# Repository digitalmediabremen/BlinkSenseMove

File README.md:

# Blink Sense Move.

A general purpose PCB/Toolkit for easy usage of sensors and actuators

# Hardware

1. maximum PCB dimensions: 100×100mm ( = 1,76/10pcs @[jlcpcb](http://jlcpcb.com) )
2. uses teensy 3.2 as mcu
3. features
  - 2 mosfets
  - h-bridge
  - amplfiers for external sensors
  - display (only dotmatrix for now, v2 will also offer pins for oled)
  - stepperdriver
  - clean audio output with lpf
  - potentiometers
  - buttons
  - patchable io
  
4. version 2 will feature
  - midi
  - choice of display
  - possibly cleaner powersolution

-----
## Pre v01

## MCU-Ideas

( supported by Arduino IDE )

1. ATmega328p (AVR, 20 MHz, 8-bit, @as_used_in(Arduino UNO)), pP 1.60€, [Datasheet](http://www.microchip.com/mymicrochip/filehandler.aspx?ddocname=en589666)
2. NXP MK20DX256 (ARM Cortex-M4, 96 MHz, 32-bit, @as_used_in(Teensy 3.2) ), pP 9.00€, [Datasheet](https://www.pjrc.com/teensy/K20P64M72SF1.pdf)
3. STM32F446RE (ARM Cortex-M4, 180 MHz, 32-bit, @as_used_in(Nucleo F446RE + Arduino for STM32)), pP 9.00€, [Datasheet](http://www.st.com/content/ccc/resource/technical/document/datasheet/65/cb/75/50/53/d6/48/24/DM00141306.pdf/files/DM00141306.pdf/jcr:content/translations/en.DM00141306.pdf)

### Boards

1) Teensy LC (approx 13 Euro) | Teensy 3.2 (Pro: Fast, Audiocapabilitys. Contra: Not super cheap)
2) Arduino Nano (Pro: Compatibilty, cheap. Contra: CH340-Driver issue with cheap Variations)

## Ideas for Features

1) Felix´ Audio Output board
2) 1 or 2 Mosfets with Diodes
3) 12v Input with good Quality Voltage converter
4) Stepper Motor Driver
5) H-Bridge
6) 7-Segment-Display
7) Add-On-Interface for stuff like Encoders or Analogsticks and similiar stuff.
8) motor board *only* ( H-bridge+mosfet, stepper-driver, PWM for high-current/loads )
9) Making the wiring Modular
10) Mic- and Piezoamp, maybe also a switchable direct out to Felix Audio out.
11) frequency devider / counter ic
12) Making it modular (plugging and using boards together, with one microcontroller)
13) encoder
14) 2 potis

## Bill of materials
- 3.5 mm jack
- AKL
- 595 (SMD?)
- IRF530 (SMD)
- 7seg/4Digit
- spannungsregler MC7805CD2TG (SMD) (1A 5V für teensy und externe komponenten)

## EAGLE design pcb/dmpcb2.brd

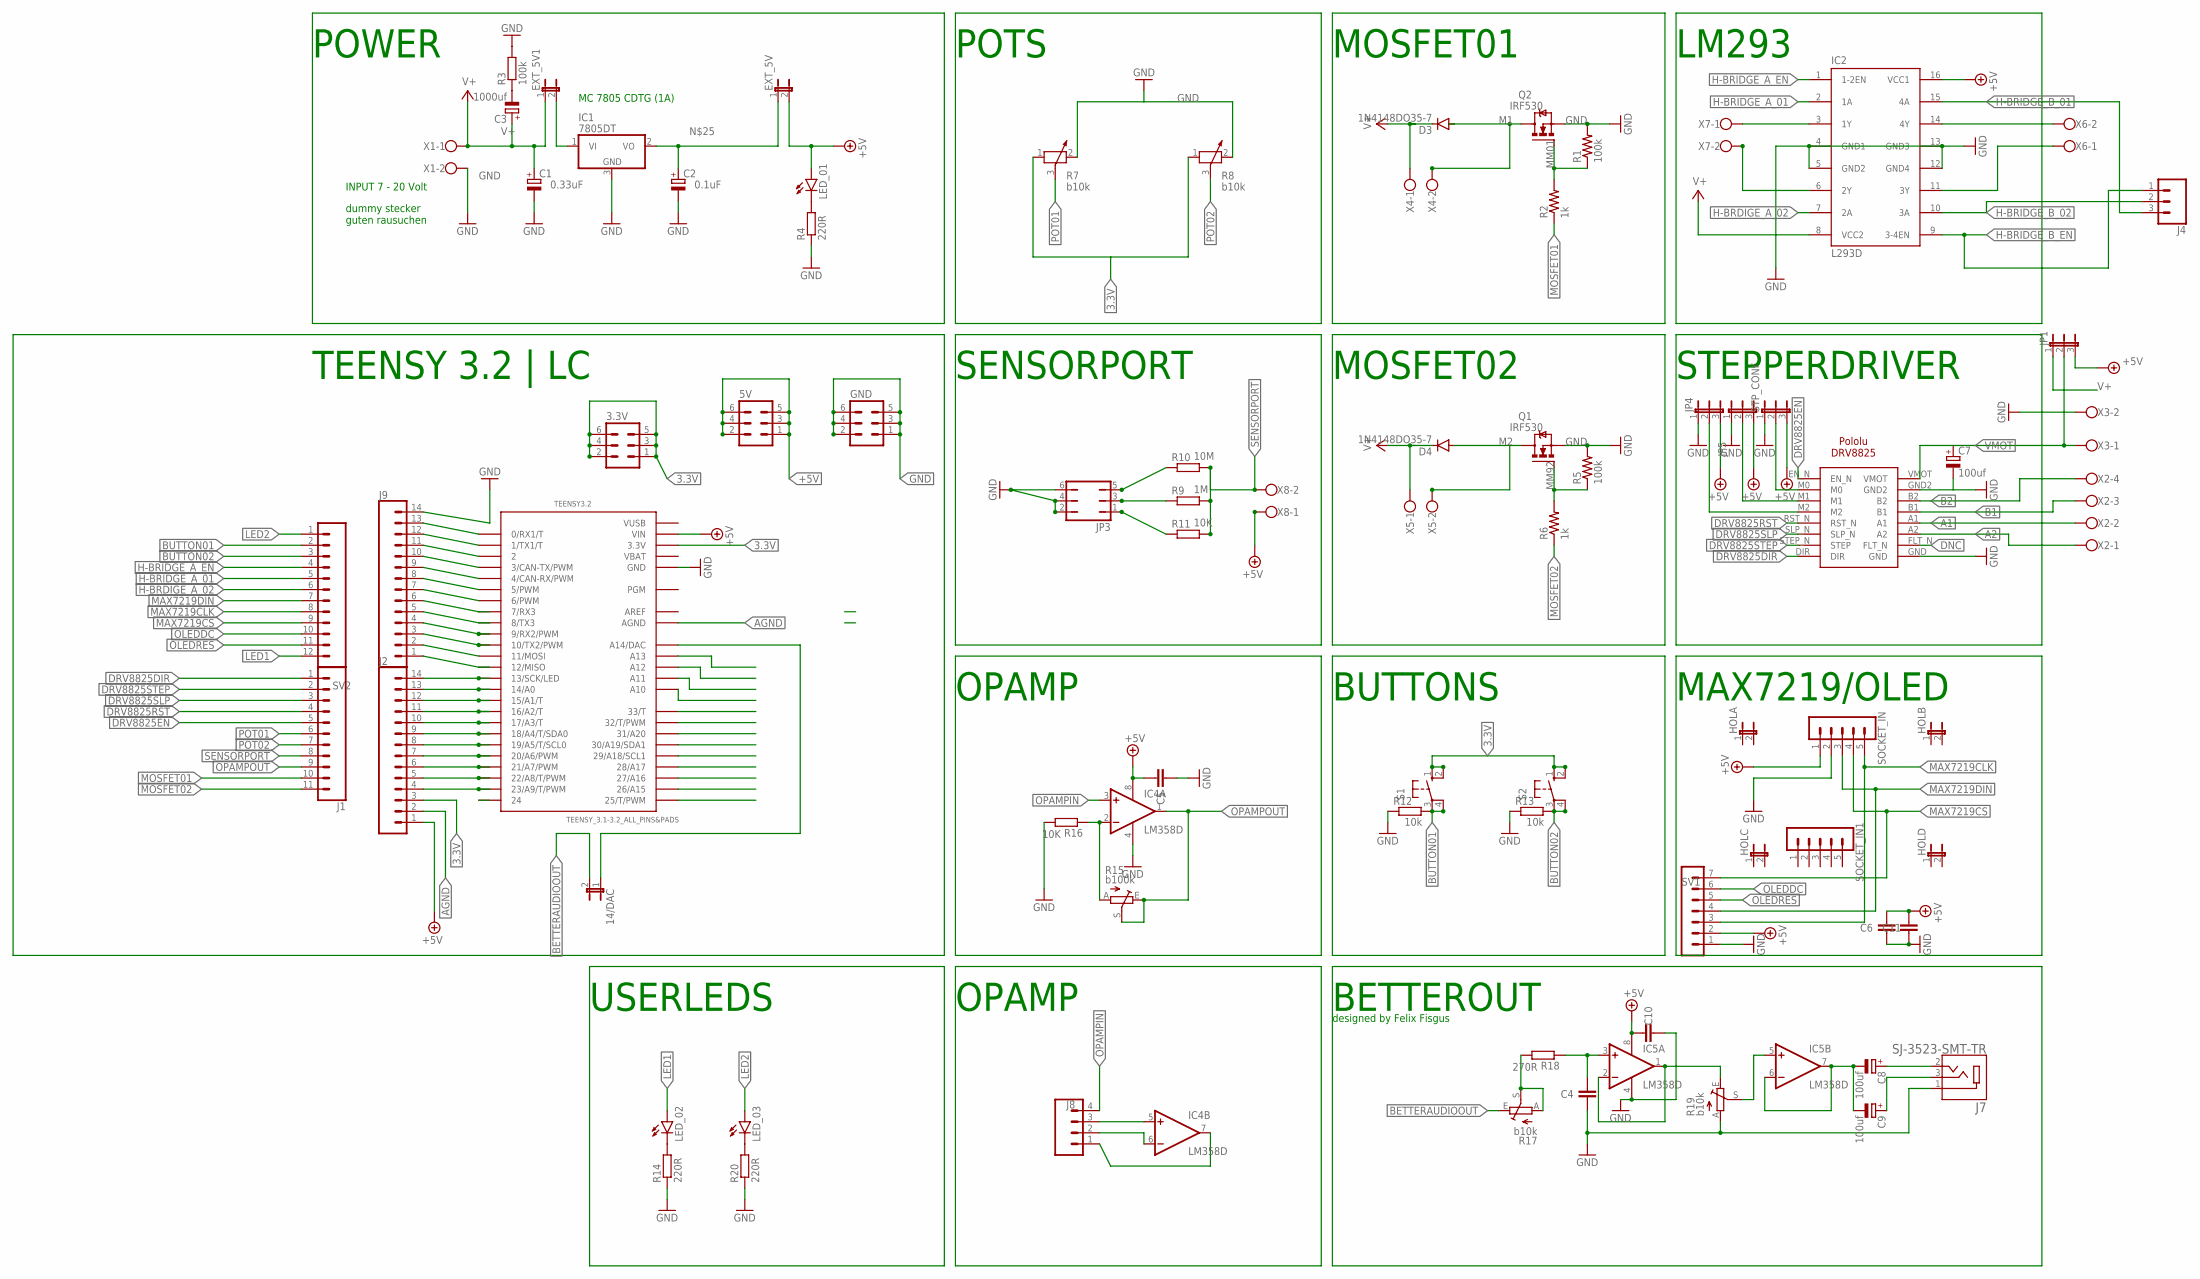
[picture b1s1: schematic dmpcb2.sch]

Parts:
3.3V, 5V: MA03-2
14/DAC: JP1E; JP1
C1: 0.33uF; SANYO-OSCON_A'
C2: 0.1uF; SANYO-OSCON_A'
C3: 1000uf; E3,5-8
C4, C5, C6, C10: 100nf; C0805
C7, C8, C9: 100uf; E5-5
C11: 10uf; C0805
D3, D4: 1N4148DO35-7; DO35-7
DRV8825: POLOLU-DRV8825
EXT_5V, EXT_5V1: JP1E; JP1
GND: MA03-2
HOLA: JP1E; JP1
HOLB: JP1E; JP1
HOLC: JP1E; JP1
HOLD: JP1E; JP1
IC1: 7805DT; TO252
IC2: L293D; DIL16
IC4, IC5: LM358D; SO08
J1: CONN_11; 1X11
J2, J9: CONN_14; 1X14
J4: CONN_03LOCK_LONGPADS; 1X03_LOCK_LONGPADS
J7: SJ-3523-SMT-TR; CUI_SJ-3523-SMT-TR
J8: CONN_04; 1X04
JP1, JP4, JP5: JP2E; JP2
JP3: JP3Q
LED_01, LED_02, LED_03: LEDSML0805; SML0805
Q1, Q2: IRF530; TO220BV
R1, R3, R5: 100k; R0805
R2, R6: 1k; R0805
R4, R14, R20: 220R; R0805
R7, R8: b10k; PT-10
R9: 1M; M0805
R10: 10M; M0805
R11, R16: 10K; M0805
R12, R13: 10k; M0805
R15: b100k; RJ9W
R17, R19: b10k; RJ9W
R18: 270R; M0805
S1, S2: 10-XX; B3F-10XX
SOCKET_IN, SOCKET_IN1: MA05-1
STP_CONF: JP2E; JP2
SV1: MA07-1
SV2: CONN_12; 1X12
TEENSY3.2: TEENSY_3.1-3.2_ALL_PINS&PADS; TEENSY_3.0-3.2_ALL_PINS_&_PADS
X1, X3, X4, X5, X6, X7, X8: W237-102
X2: W237-4

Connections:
3.3V: 3.3V.1, 3.3V.2, 3.3V.3, 3.3V.4, 3.3V.5, 3.3V.6, J2.3, R7.1, R8.1, S1.1 (S), S1.2 (S1), S2.1 (S), S2.2 (S1), TEENSY3.2.3.3V, TEENSY3.2.3.3V1 (3.3V), TEENSY3.2.3.3V2 (3.3V)
+5V: 5V.1, 5V.2, 5V.3, 5V.4, 5V.5, 5V.6, C5.1, C6.1, C10.2, C11.1, EXT_5V.2, IC2.16 (VCC1), IC4.8 (V+), IC5.8 (V+), J2.1, JP1.3, JP4.3, JP5.3, LED_01.A, SOCKET_IN.1, STP_CONF.3, SV1.2, TEENSY3.2.VIN, X8.1
A1: DRV8825.A1, X2.2
A2: DRV8825.A2, X2.1
AGND: J2.2, TEENSY3.2.AGND
AREF: TEENSY3.2.AREF
B1: DRV8825.B1, X2.3
B2: DRV8825.B2, X2.4
BETTERAUDIOOUT: 14/DAC.2, R17.E
BUTTON01: R12.2, S1.3, S1.4 (P1), SV2.2
BUTTON02: R13.2, S2.3, S2.4 (P1), SV2.3
DNC: DRV8825.FLT_N
DRV8825DIR: DRV8825.DIR, J1.1
DRV8825EN: DRV8825.EN_N, J1.5
DRV8825RST: DRV8825.RST_N, J1.4
DRV8825SLP: DRV8825.SLP_N, J1.3
DRV8825STEP: DRV8825.STEP_N (STEP), J1.2
GND: C1.-, C2.-, C4.2, C5.2, C6.2, C7.-, C10.1, C11.2, DRV8825.GND, DRV8825.GND2, GND.1, GND.2, GND.3, GND.4, GND.5, GND.6, IC1.3 (GND), IC2.4 (GND1), IC2.5 (GND2), IC2.12 (GND4), IC2.13 (GND3), IC4.4 (V-), IC5.4 (V-), J7.1, J9.14, JP3.2, JP3.4, JP3.6, JP4.1, JP5.1, Q1.S, Q2.S, R1.2, R3.2, R4.1, R5.2, R7.2, R8.2, R12.1, R13.1, R14.1, R16.2, R19.A, R20.1, SOCKET_IN.2, STP_CONF.1, SV1.1, TEENSY3.2.GND, TEENSY3.2.GND1 (GND), TEENSY3.2.GND2 (GND), X1.2, X3.2
H-BRDIGE_A_02: IC2.7 (2A), SV2.6
H-BRIDGE_A_01: IC2.2 (1A), SV2.5
H-BRIDGE_A_EN: IC2.1 (1-2EN), SV2.4
H-BRIDGE_B_01: IC2.15 (4A), J4.3
H-BRIDGE_B_02: IC2.10 (3A), J4.2
H-BRIDGE_B_EN: IC2.9 (3-4EN), J4.1
LED1: LED_02.A, SV2.12
LED2: LED_03.A, SV2.1
M1: D3.A, Q2.D, X4.2
M2: D4.A, Q1.D, X5.2
MAX7219CLK: SOCKET_IN.5, SV1.3, SV2.8
MAX7219CS: SOCKET_IN.4, SV1.7, SV2.9
MAX7219DIN: SOCKET_IN.3, SV1.4, SV2.7
MM01: Q2.G, R1.1, R2.2
MM92: Q1.G, R5.1, R6.2
MOSFET01: J1.10, R2.1
MOSFET02: J1.11, R6.1
unnamed: IC2.3 (1Y), X7.1
unnamed: IC2.6 (2Y), X7.2
unnamed: C3.-, R3.1
unnamed: LED_01.C, R4.2
unnamed: IC2.14 (4Y), X6.2
unnamed: IC2.11 (3Y), X6.1
unnamed: JP3.5, R10.1
unnamed: JP3.3, R9.1
unnamed: JP3.1, R11.1
unnamed: EXT_5V1.2, IC1.1 (VI)
unnamed: IC4.5 (+IN), J8.3
unnamed: J2.4, TEENSY3.2.23/A9 (23/A9/T/PWM)
unnamed: C2.+, EXT_5V.1, IC1.2 (VO)
unnamed: J2.5, TEENSY3.2.22/A8 (22/A8/T/PWM)
unnamed: J2.6, TEENSY3.2.21/A7 (21/A7/PWM)
unnamed: J2.7, TEENSY3.2.20/A6 (20/A6/PWM)
unnamed: J2.8, TEENSY3.2.19/A5 (19/A5/T/SCL0)
unnamed: J2.9, TEENSY3.2.18/A4 (18/A4/T/SDA0)
unnamed: J2.10, TEENSY3.2.17/A3 (17/A3/T)
unnamed: J2.11, TEENSY3.2.16/A2 (16/A2/T)
unnamed: J2.12, TEENSY3.2.15/A1 (15/A1/T)
unnamed: J2.13, TEENSY3.2.14/A0
unnamed: J2.14, TEENSY3.2.13 (13/SCK/LED)
unnamed: J9.1, TEENSY3.2.12 (12/MISO)
unnamed: J9.2, TEENSY3.2.11 (11/MOSI)
unnamed: J9.3, TEENSY3.2.10 (10/TX2/PWM)
unnamed: J9.4, TEENSY3.2.9 (9/RX2/PWM)
unnamed: J9.5, TEENSY3.2.8 (8/TX3)
unnamed: J9.6, TEENSY3.2.7 (7/RX3)
unnamed: 14/DAC.1, TEENSY3.2.RESET/DAC (A14/DAC)
unnamed: DRV8825.M2, JP4.2
unnamed: DRV8825.M1, JP5.2
unnamed: DRV8825.M0, STP_CONF.2
unnamed: J9.12, TEENSY3.2.1 (1/TX1/T)
unnamed: J9.13, TEENSY3.2.0 (0/RX1/T)
unnamed: IC4.2 (-IN), R15.A, R16.1
unnamed: LED_02.C, R14.2
unnamed: C8.+, J7.2
unnamed: R17.A, R17.S, R18.2
unnamed: C4.1, IC5.3 (+IN), R18.1
unnamed: IC5.1 (OUT), IC5.2 (-IN), R19.E
unnamed: IC4.6 (-IN), J8.2
unnamed: IC5.5 (+IN), R19.S
unnamed: C8.-, C9.-, IC5.6 (-IN), IC5.7 (OUT)
unnamed: C9.+, J7.3
unnamed: IC4.7 (OUT), J8.1
unnamed: LED_03.C, R20.2
OLEDDC: SV1.6, SV2.10
OLEDRES: SV1.5, SV2.11
OPAMPIN: IC4.3 (+IN), J8.4
OPAMPOUT: IC4.1 (OUT), J1.9, R15.E, R15.S
PIN2: J9.11, TEENSY3.2.2
PIN3: J9.10, TEENSY3.2.3 (3/CAN-TX/PWM)
PIN4: J9.9, TEENSY3.2.4 (4/CAN-RX/PWM)
PIN5: J9.8, TEENSY3.2.5 (5/PWM)
PIN6: J9.7, TEENSY3.2.6 (6/PWM)
POT01: J1.6, R7.3
POT02: J1.7, R8.3
SENSORPORT: J1.8, R9.2, R10.2, R11.2, X8.2
V+: C1.+, C3.+, D3.C, D4.C, EXT_5V1.1, IC2.8 (VCC2), JP1.1, X1.1, X4.1, X5.1
VBAT: TEENSY3.2.VBAT
VMOT: C7.+, DRV8825.VMOT, JP1.2, X3.1
VUSB: TEENSY3.2.VUSB

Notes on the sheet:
POWER
INPUT 7 - 20 Volt
MC 7805 CDTG (1A)
TEENSY 3.2 | LC
dummy stecker guten rausuchen
MOSFET01
LM293
MOSFET02
POTS
STEPPERDRIVER
SENSORPORT
BUTTONS
MAX7219/OLED
OPAMP
BETTEROUT
designed by Felix Fisgus
USERLEDS

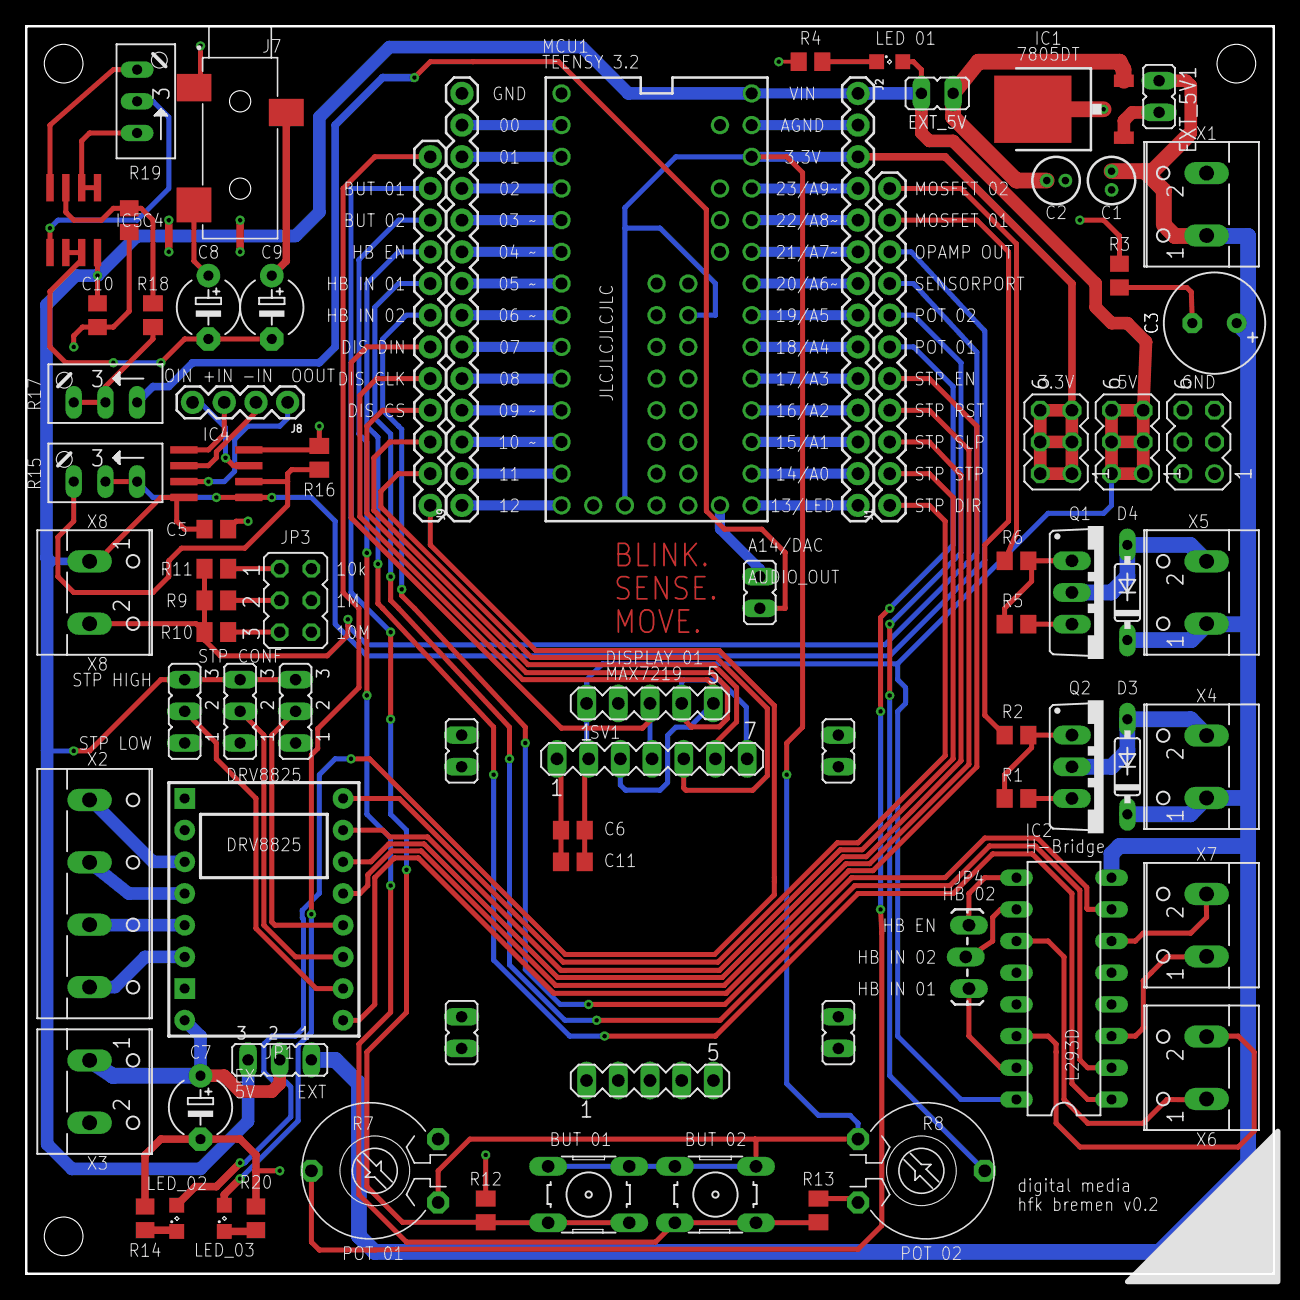
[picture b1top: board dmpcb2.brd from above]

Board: 2 copper layers, 100.0 x 100.0 mm, 79 parts (0 on the bottom side), 94 nets.

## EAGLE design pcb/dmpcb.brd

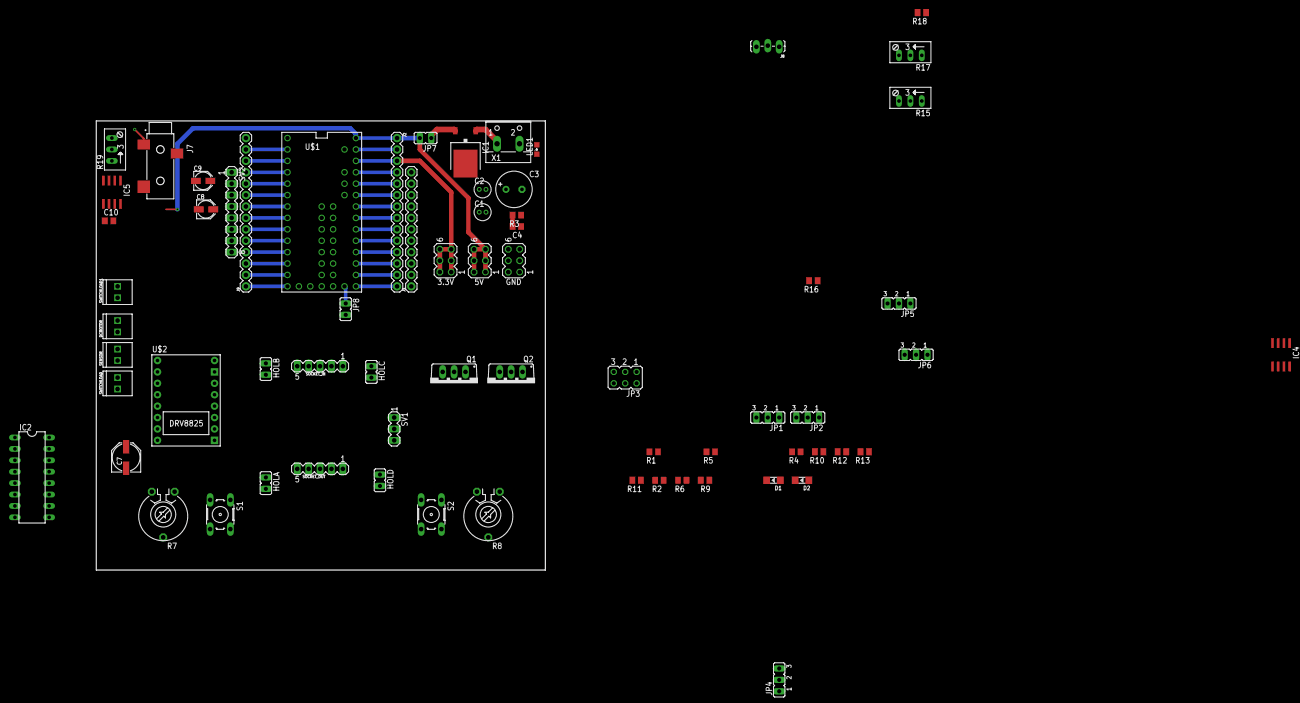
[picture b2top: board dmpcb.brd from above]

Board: 2 copper layers, 100.0 x 100.0 mm, 68 parts (0 on the bottom side), 80 nets.

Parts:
3.3V, 5V: MA03-2
C1: 0.33uF; SANYO-OSCON_A'
C2: 0.1uF; SANYO-OSCON_A'
C3: 1000uf; E3,5-8
C4, C10: 100nf; C0805
C7: 100uf; PANASONIC_D
C8, C9: 100uf; PANASONIC_B
D1, D2: 1N4148; LL-34
DCMOTOR: 1X02_2.54_SCREWTERM
GND: MA03-2
HOLA: JP1
HOLB: JP1
HOLC: JP1
HOLD: JP1
IC1: 7805DT; TO252
IC2: L293D; DIL16
IC4, IC5: LM358D; SO08
J1: 1X11
J2, J9: 1X14
J7: SJ-3523-SMT-TR; CUI_SJ-3523-SMT-TR
J8: 1X03_LOCK_LONGPADS
JP1, JP2, JP4, JP5, JP6: JP2
JP3: JP3Q
JP7, JP8: JP1
LED1: SML0805
Q1, Q2: IRF530; TO220BV
R1, R3, R5: 100k; R0805
R2, R6: 1k; R0805
R4: 220; R0805
R7, R8: b10k; PT-10
R9: 1M; M0805
R10: 10M; M0805
R11, R16: 10K; M0805
R12, R13: 10k; M0805
R15: b100k; RJ9W
R17, R19: b10k; RJ9W
R18: 270R; M0805
S1, S2: B3F-10XX
SENSOR: 1X02_2.54_SCREWTERM
SOCKET_IN: MA05-1
SOCKET_OUT: MA05-1
SV1: MA03-1
SV2: MA08-1
SWITCHLOAD, SWITCHLOAD1: 1X02_2.54_SCREWTERM
U$1: TEENSY_3.1-3.2_ALL_PINS&PADS; TEENSY_3.0-3.2_ALL_PINS_&_PADS
U$2: POLOLU-DRV8825
X1: W237-102

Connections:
3.3V: 3.3V.1, 3.3V.2, 3.3V.3, 3.3V.4, 3.3V.5, 3.3V.6, J2.3, R7.1, R8.1, U$1.3.3V, U$1.3.3V1, U$1.3.3V2
+5V: 5V.1, 5V.2, 5V.3, 5V.4, 5V.5, 5V.6, C10.2, IC2.16, IC4.8, IC5.8, J2.1, JP4.3, JP5.3, JP6.3, JP7.2, SENSOR.P2, SOCKET_IN.1, U$1.VIN
AGND: J2.2, U$1.AGND
BETTERAUDIOOUT: JP8.2, R17.E
BUTTON01: R12.2, S1.3, S1.4, SV2.1
BUTTON02: R13.2, S2.3, S2.4, SV2.2
D: JP1.2, JP2.2, Q1.D, Q2.D, SWITCHLOAD.P1, SWITCHLOAD1.P1
DRV8825DIR: J1.2, U$2.DIR
DRV8825EN: J1.1, U$2.EN_N
DRV8825RST: J1.4, U$2.RST_N
DRV8825SLP: J1.5, U$2.SLP_N
DRV8825STEP: J1.3, U$2.STEP_N
G: Q1.G, Q2.G, R1.1, R2.2, R5.1, R6.2
GND: C1.-, C2.-, C4.2, C7.-, C10.1, GND.1, GND.2, GND.3, GND.4, GND.5, GND.6, IC1.3, IC2.4, IC2.5, IC2.12, IC2.13, IC4.4, IC5.4, J7.1, J9.14, JP3.2, JP3.4, JP3.6, JP4.1, JP5.1, JP6.1, R3.2, R4.1, R7.2, R8.2, R12.1, R13.1, R16.2, R19.A, SOCKET_IN.2, U$1.GND, U$1.GND1, U$1.GND2, U$2.GND, U$2.GND2, X1.2
LM293EN: IC2.1, SV2.3
LM293IN01: IC2.2, SV2.4
LM293IN02: IC2.7, SV2.5
MAX7219CLK: SOCKET_IN.5, SV1.1, SV2.7
MAX7219CS: SOCKET_IN.4, SV1.2, SV2.8
MAX7219DIN: SOCKET_IN.3, SV1.3, SV2.6
MOSFET01: J1.10, R2.1
MOSFET02: J1.11, R6.1
unnamed: DCMOTOR.P2, IC2.3
unnamed: DCMOTOR.P1, IC2.6
unnamed: C3.-, R3.1
unnamed: LED1.C, R4.2
unnamed: D2.A, JP2.3
unnamed: D1.A, JP1.3
unnamed: JP3.5, R10.1
unnamed: JP3.3, R9.1
unnamed: JP3.1, R11.1
unnamed: S1.1, S1.2
unnamed: IC4.5, J8.3
unnamed: S2.1, S2.2
unnamed: J2.4, U$1.23/A9
unnamed: C2.+, IC1.2, JP7.1, LED1.A
unnamed: J2.5, U$1.22/A8
unnamed: J2.6, U$1.21/A7
unnamed: J2.7, U$1.20/A6
unnamed: J2.8, U$1.19/A5
unnamed: J2.9, U$1.18/A4
unnamed: J2.10, U$1.17/A3
unnamed: J2.11, U$1.16/A2
unnamed: J2.12, U$1.15/A1
unnamed: J2.13, U$1.14/A0
unnamed: J2.14, U$1.13
unnamed: J9.1, U$1.12
unnamed: J9.2, U$1.11
unnamed: J9.3, U$1.10
unnamed: J9.4, U$1.9
unnamed: J9.5, U$1.8
unnamed: J9.6, U$1.7
unnamed: JP8.1, U$1.RESET/DAC
unnamed: JP4.2, U$2.M2
unnamed: JP5.2, U$2.M1
unnamed: JP6.2, U$2.M0
unnamed: J9.12, U$1.1
unnamed: J9.13, U$1.0
unnamed: IC4.2, R15.A, R16.1
unnamed: C8.+, J7.2
unnamed: R17.A, R17.S, R18.2
unnamed: C4.1, IC5.3, R18.1
unnamed: IC5.1, IC5.2, R19.E
unnamed: IC4.6, J8.2
unnamed: IC5.5, R19.S
unnamed: C8.-, C9.-, IC5.6, IC5.7
unnamed: C9.+, J7.3
unnamed: IC4.7, J8.1
OPAMPOUT: IC4.1, J1.9, R15.E, R15.S
PIN2: J9.11, U$1.2
PIN3: J9.10, U$1.3
PIN4: J9.9, U$1.4
PIN5: J9.8, U$1.5
PIN6: J9.7, U$1.6
POT01: J1.6, R7.3
POT02: J1.7, R8.3
S: Q1.S, Q2.S, R1.2, R5.2
SENSORPORT: J1.8, R9.2, R10.2, R11.2, SENSOR.P1
V+: C1.+, C3.+, D1.C, D2.C, IC1.1, IC2.8, JP1.1, JP2.1, SWITCHLOAD.P2, SWITCHLOAD1.P2, X1.1
VMOT: C7.+, U$2.VMOT

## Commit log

2018-12-05 Added some first ideas
2018-12-12 added MCUs, distinguished between MCUs + boards
2018-12-12 updated features
2018-12-12 Added some feature Ideas
2018-12-13 ralf change
2018-12-14 teens header
2018-12-14 eagle lck file..
2018-12-14 provisorische power suppy / spannungsregler
2019-01-04 added mosfet into schematic, wasn´t able to find teensy 3.1 lib, please add to repo
2019-01-05 added lm293 to schematic
2019-01-10 added feature to list ´12) making it modular´
2019-01-11 added .gitignore
2019-01-11 added encoder and pots to idealsist
2019-01-17 added Filtercap, powerled, doubled up the mosfet, also added possiblitiy to jump protectiondiode for mosfets
2019-01-17 added stepperdriver and pots, lm293 still needs some corrections
2019-01-18 cleanup, nothing else
2019-02-18 added Todo to file, buttons, sensorport with variable resistors (had the idea of maybe enabling one of the potis to be jumpered in as a variable resistor?) and 12v to lm293
2019-02-18 changed portlayout, added DNC to the pins in the middle of the teensy
2019-02-22 changed some parts around, added max7219 (only needed if we chose discrete implementation, not the readymade board -> because more expensive), changed the pins around on the teensy. The stepperdriver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
2019-02-22 deleted and removed faulty .brd file
2019-02-22 added fresh .brd file
2019-02-22 Holy hell, I have no idea what I am doing. This is so different from kicad. brb, gone to watch tutorials....
2019-02-26 don´t know what changed. well...
2019-03-19 found footprint for drv8825 carrier board, included it into schematic
2019-06-01 added other teensy lib, has better pin spacing, also added breakout jumpers for all pins (-RX and TX)
2019-06-02 fixed drv8825, also added lm358
2019-06-02 need to add custom component for dotmatrix display
2019-06-03 added jumper around 7805, if 5v load is bigger than 1Amp
2019-06-05 added felix' better audio output (thank you felix). still need to find use for one half opamp. Ideas?
2019-06-05 added missing decoupling cap
2019-06-06 corrected sensorport and changed the second half of the lm358 to a freely user-configurable setup
2019-08-15 borading..
2019-08-15 borading2..
2019-08-16 routing done
2019-08-16 started to add part references and values, also started adding pin names and similar. tried adding nice graphics as bmp but failed horribly...
2019-08-20 added component names, deleted component values. still need to add names to AKLs. Maybe drawing zones on the board would be good?
2019-08-20 added names fand outs for AKLS
2019-08-20 fixed some wire stubs
2019-08-20 fixed mirrored AKLs
2019-08-21 this is a test
2019-08-21 removing tes
2020-03-12 Create toDo-for-v2
2020-03-12 Rename toDo-for-v2 to toDo-for-v2.md
2020-05-28 ver 2
2020-05-28 ordered version
2020-06-10 issues added and fixed
2020-06-10 added possibilty to jump out the lm7805
2020-06-10 changed powerconnector
2020-06-18 Update Reponame
2020-06-25 moved bypass caps
2020-06-25 fixed lists
2020-06-29 added support for second display, but only is possible at the time
2020-06-29 added second jack for midi, not too sure if position is good. thinking about putting pads on the bottom of the board and making the jack optional?
2020-07-02 moved second display a bit upwards
2020-07-02 remove test.md
2020-07-13 removed second 3.5mm jack, drc comes back clean
2020-07-14 changed naming (v0.2 instead of v.02), some other small fixes
2020-07-14 Delete toDo-for-v2.md
    Changes were implemented.
2020-07-15 screws fit
2020-07-18 added user leds and labeling for opamp
2020-07-18 some final cleanup work, orderd first v0.2 pcbs
2020-08-05 added BOM
2020-08-05 added BOM for v2
2020-08-07 moved some files
2020-08-07 renamed v02 bom and added v02 schematic as pdf
2020-08-26 added file for config. wiki would be cool
2020-09-01 started off the system.h file
2020-09-01 deleting some obsolete stuff
2020-09-03 cleanup
2020-09-04 added blink example
2020-09-04 added sense example/Sensorport, added discription into blink example
2020-09-04 added button sketch
2020-09-04 added potetiometer sketch
2020-09-06 added examples for sound and dc motor
2020-09-08 added more examples
2020-09-08 added example library
2020-09-13 comments, comments, comments. also, some styling
2020-09-13 whoops
2020-09-13 added library
2020-09-13 keywords. anymore ideas?
2020-09-14 changes, changes
2020-09-14 cleaned up
2020-09-14 changed libname to BlinkSenseMove, also removed some unmotivated empty lines
2020-09-14 simplified oled example, added dotmatrix example, but did not start it yet
2020-09-22 added dotmatrixdisplay example, as well as a zip of the lib
2020-09-29 mosfet example...
2020-09-29 added release build script, cleaned up

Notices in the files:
parts and their libraries:
SparkFun-Connectors: Licensing: Creative Commons ShareAlike 4.0 International - https://creativecommons.org/licenses/by-sa/4.0
